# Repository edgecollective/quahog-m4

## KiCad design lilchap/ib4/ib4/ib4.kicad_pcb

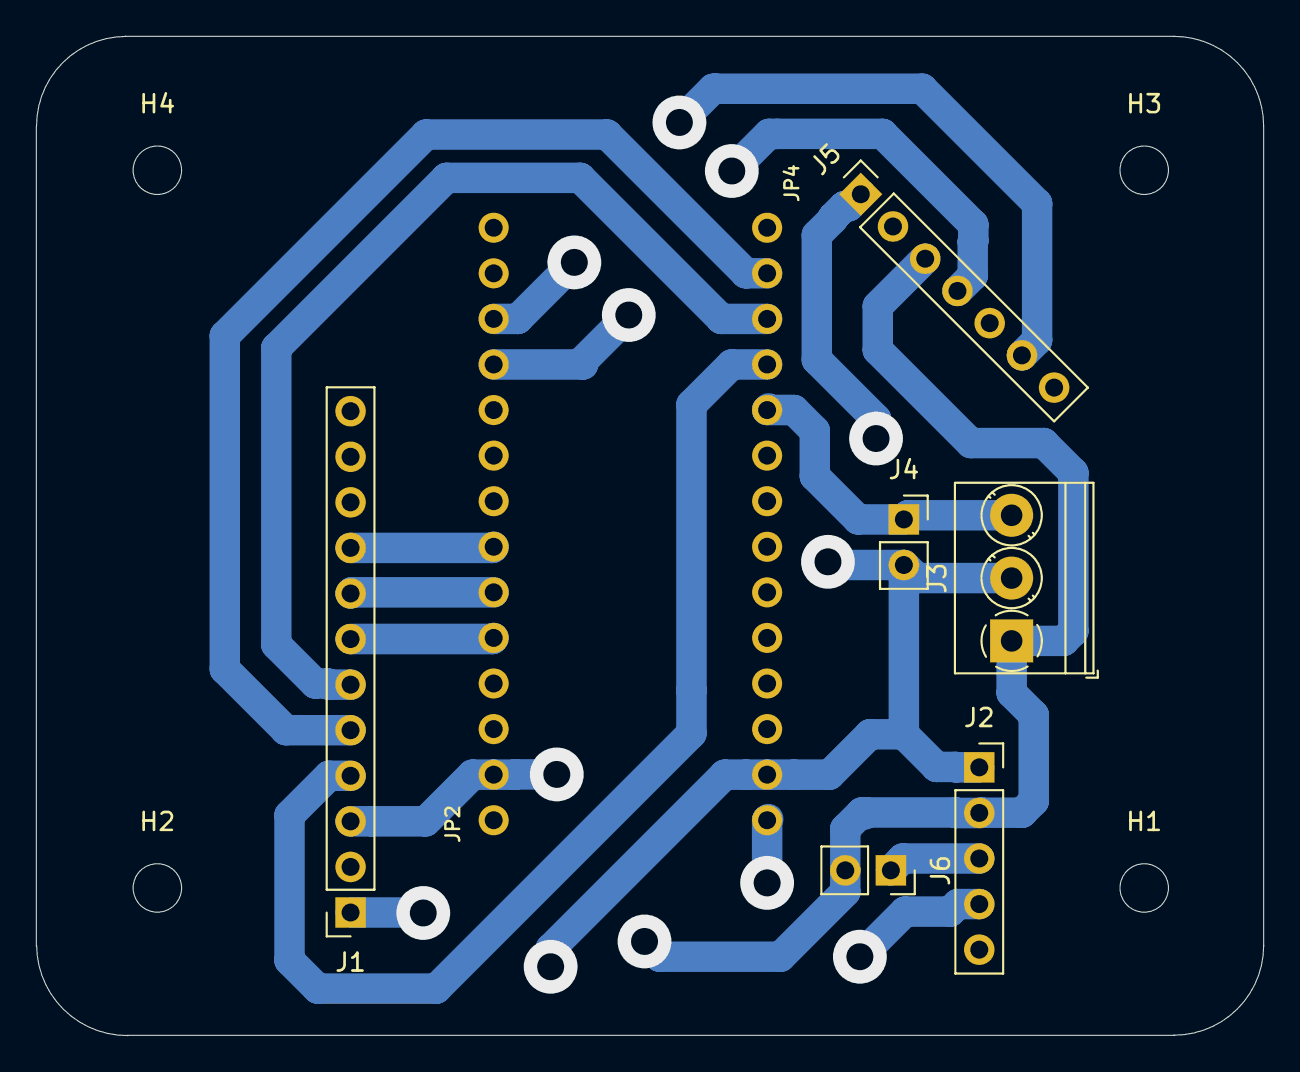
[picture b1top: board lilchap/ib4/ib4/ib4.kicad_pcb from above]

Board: 4 copper layers, 68.4 x 55.7 mm, 12 parts (0 on the bottom side), 13 nets.

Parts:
H1, H2, H3, H4: MountingHole; MountingHole_2.7mm_M2.5
J1: Conn_01x12_Female; PinSocket_1x12_P2.54mm_Vertical
J2: Conn_01x05_Female; PinSocket_1x05_P2.54mm_Vertical
J3: Conn_01x03_Female; TerminalBlock_Phoenix_PT-1,5-3-3.5-H_1x03_P3.50mm_Horizontal
J4, J6: Conn_01x02_Female; PinSocket_1x02_P2.54mm_Vertical
J5: Conn_01x07_Female; PinSocket_1x07_P2.54mm_Vertical
JP2, JP4: HEADER-1X14; 1X14_ROUND70

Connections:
+3V3: J1.1, J2.1, J3.2, J4.2, J5.1, JP4.13
A5: J3.3, J4.1, JP4.5
DELAY: J2.3, J6.1
DRV: J2.4, JP4.14
E_BUSY: J1.8, JP2.6
E_CS: J1.7, JP2.5
E_~RST: J1.9, JP2.7
GND: J1.3, J2.2, J3.1, J5.3, J6.2, JP2.2
MISO: J1.5, JP4.2
MOSI: J1.6, JP4.3
SCK: J1.4, JP4.4
SCL: J5.4, JP2.11
SDA: J5.6, JP2.12

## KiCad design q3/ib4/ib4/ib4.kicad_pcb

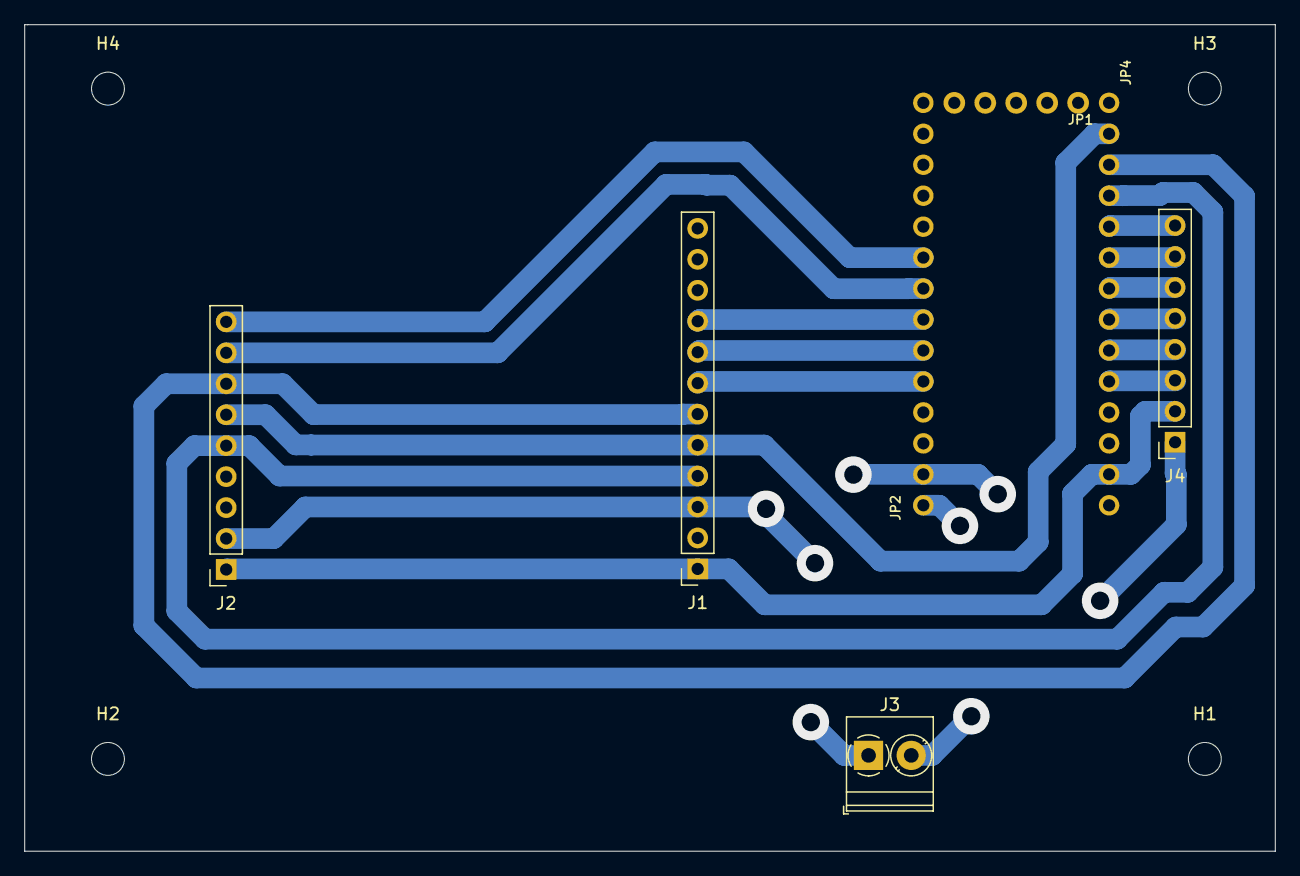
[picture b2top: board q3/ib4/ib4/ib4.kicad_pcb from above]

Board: 4 copper layers, 102.6 x 67.8 mm, 11 parts (0 on the bottom side), 17 nets.

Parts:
H1, H2, H3, H4: MountingHole; MountingHole_2.7mm_M2.5
J1: Conn_01x12_Female; PinSocket_1x12_P2.54mm_Vertical
J2: Conn_01x09_Female; PinSocket_1x09_P2.54mm_Vertical
J3: Screw_Terminal_01x02; TerminalBlock_Phoenix_PT-1,5-2-3.5-H_1x02_P3.50mm_Horizontal
J4: Conn_01x08_Female; PinSocket_1x08_P2.54mm_Vertical
JP1: HEADER-1X570MIL; 1X05_ROUND_70
JP2, JP4: HEADER-1X14; 1X14_ROUND70

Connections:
+3V3: J1.1, J2.1, J4.2, JP4.13
/A0: J4.3, JP4.10
/A1: J4.4, JP4.9
/A2: J4.5, JP4.8
/A3: J4.6, JP4.7
/A4: J4.7, JP4.6
/A5: J4.8, JP4.5
E_BUSY: J1.8, JP2.6
E_CS: J1.7, JP2.5
E_~RST: J1.9, JP2.7
GND: J1.3, J2.2, J3.1, J4.1, JP2.2
L_CS: J2.8, JP2.8
L_RST: J2.9, JP2.9
MISO: J1.5, J2.6, JP4.2
MOSI: J1.6, J2.7, JP4.3
SCK: J1.4, J2.5, JP4.4
VBAT: J3.2, JP2.1

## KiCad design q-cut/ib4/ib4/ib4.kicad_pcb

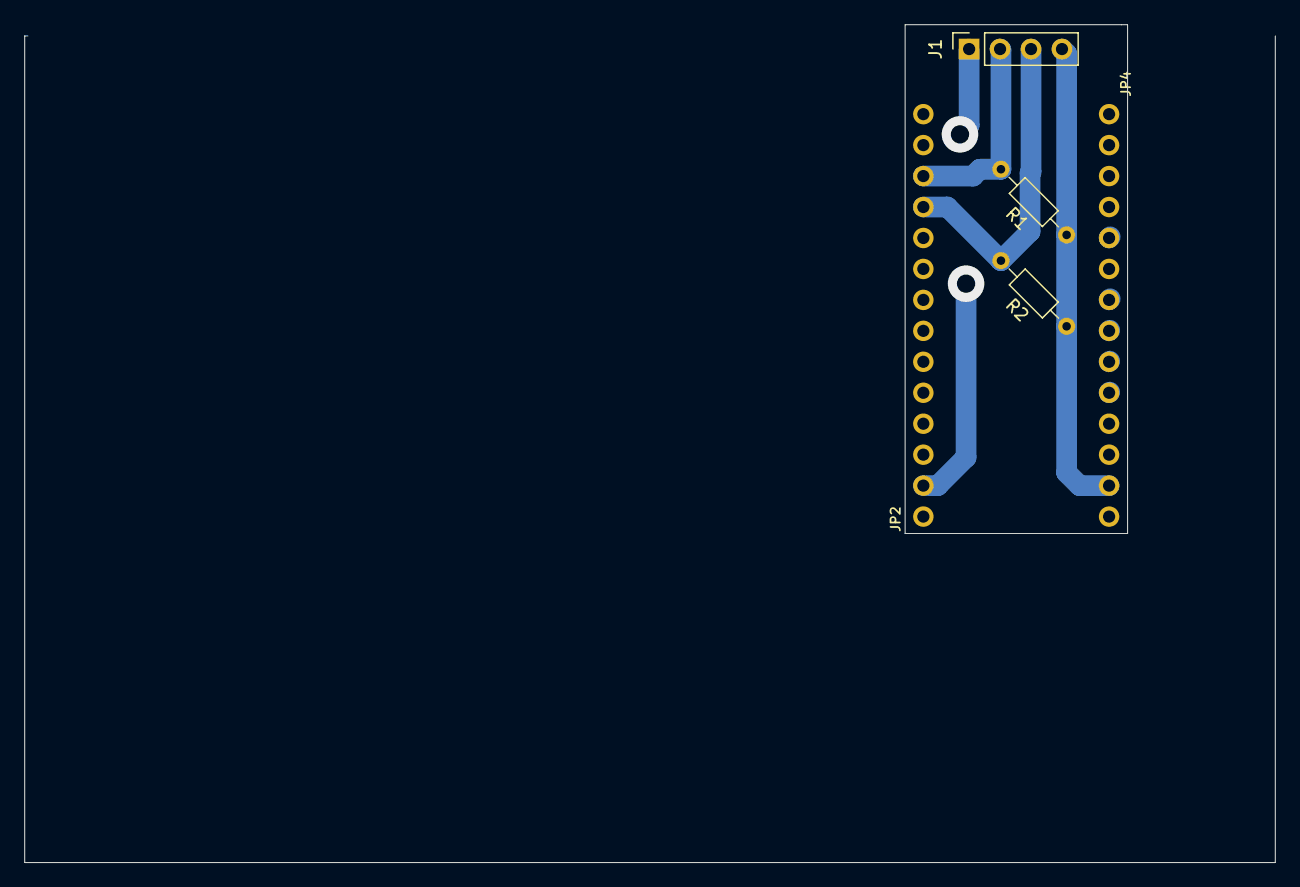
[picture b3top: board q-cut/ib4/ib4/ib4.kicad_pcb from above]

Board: 4 copper layers, 18.2 x 41.8 mm, 5 parts (0 on the bottom side), 4 nets.

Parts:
J1: Conn_01x04_Female; PinSocket_1x04_P2.54mm_Vertical
JP2, JP4: HEADER-1X14; 1X14_ROUND70
R1, R2: R; R_Axial_DIN0204_L3.6mm_D1.6mm_P7.62mm_Horizontal

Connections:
+3V3: J1.4, JP4.13, R1.1, R2.1
GND: J1.1, JP2.2
SCL: J1.3, JP2.11, R2.2
SDA: J1.2, JP2.12, R1.2

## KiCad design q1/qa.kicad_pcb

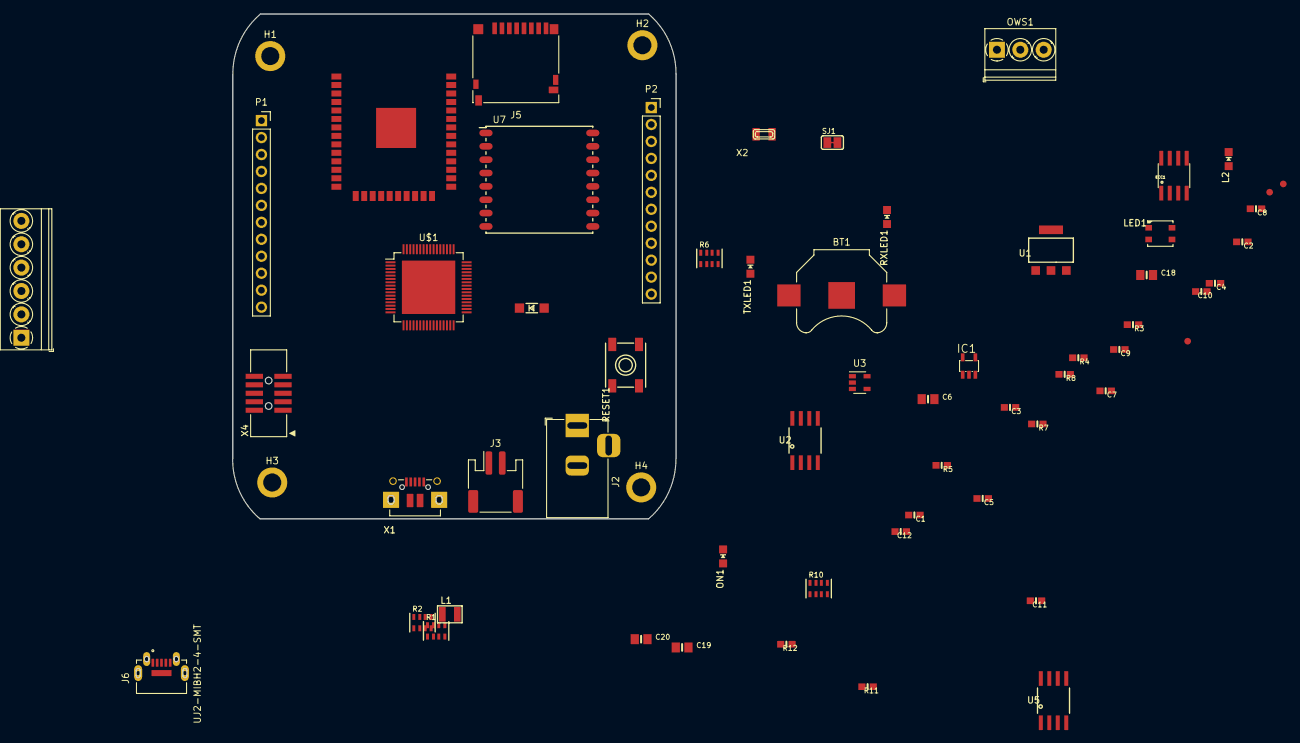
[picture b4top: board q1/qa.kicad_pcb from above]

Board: 2 copper layers, 63 parts (0 on the bottom side), 59 nets, no tracks yet.

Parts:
BT1: Battery_Cell; BatteryHolder_Keystone_3000_1x12mm
C1, C4: 22pF; 0603-NO
C2: 0.1uF; 0603-NO
C3, C7, C8, C9, C10, C11, C12: .1u; 0603-NO
C5: 1uF; 0603-NO
C6, C18, C19, C20: 10uF; 0805-NO
D1: D; SOD-123
ECC1: ATECC108; SOIC8
FD1, FD2, FD3: FIDUCIAL_1MM
H1, H2, H3, H4: MountingHole; MountingHole_2.7mm_M2.5_ISO14580_Pad
IC1: 74AHC1G125; SOT23-5L
J2: Barrel_Jack; BarrelJack_Horizontal
J3: Conn_01x02_Female; JST_PH_S2B-PH-SM4-TB_1x02-1MP_P2.00mm_Horizontal
J5: Connector_Micro_SD_Card; microSD_HC_Hirose_DM3D-SF
J6: UJ2-MIBH2-4-SMT; CUI_UJ2-MIBH2-4-SMT
J8: Screw_Terminal_01x06; TerminalBlock_Phoenix_PT-1,5-6-3.5-H_1x06_P3.50mm_Horizontal
L1: 10uH; INDUCTOR_1007
L2: RED; CHIPLED_0805_NOOUTLINE
LED1: WS2812B3535; LED3535
ON1: GREEN; CHIPLED_0805_NOOUTLINE
OWS1: Screw_Terminal_01x03; TerminalBlock_Phoenix_PT-1,5-3-3.5-H_1x03_P3.50mm_Horizontal
P1, P2: Conn_01x12_Female; PinSocket_1x12_P2.54mm_Vertical
R1: 10K; RESPACK_4X0603
R2, R6: R; RESPACK_4X0603
R3, R4, R5, R7: R; 0603-NO
R8, R12: 10K; 0603-NO
R10: 1K; RESPACK_4X0603
R11: 1K; 0603-NO
RESET1: EVQQ 6mm; EVQ-Q2_SMALLER
RXLED1: YELLOW; CHIPLED_0805_NOOUTLINE
SJ1: AREF_3V; SOLDERJUMPER_CLOSEDWIRE
TXLED1: YELLOW; CHIPLED_0805_NOOUTLINE
U1: tpl5110; SOT223-R
U2: CUI VX7805; SOIC8_208MIL
U3: AP2112K-3.3; SOT-23-5
U5: GD25Q16; SOIC8_208MIL
U7: RFM95HW; RFM95
U$1: ATSAMD51J19; TQFP-64-1EP_10x10mm_P0.5mm_EP8x8mm
X1: 20329; 4UCONN_20329_V2
X2: 32.768; XTAL3215
X4: 2x5 0.05" SWD; 2X05_1.27MM_BOX_POSTS
X5: ESP32_WROOM32; WROOM32

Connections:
3.3V: C7.2, C8.2, C9.2, C10.2, C11.2, C18.1, C19.1, C20.1, ECC1.8, IC1.5, J5.4, LED1.2, ON1.A, R1.1, R1.3, R1.4, R1.7, R8.2, R11.2, RXLED1.A, SJ1.1, TXLED1.A, U5.8, U7.13, U$1.8, U$1.21, U$1.34, U$1.48, U$1.56, X4.1, X5.2
/A0: P1.1, U$1.3
/A1: P1.2, U$1.14
/A2: P1.3, U$1.15
/A3: P1.4, U$1.61
/A4: P1.5, U$1.11
/A5: P1.6, U$1.12
/AREF: C12.1, SJ1.2, U$1.4
/D0: P1.7, U$1.44
/D2: P1.8, U$1.40
/D3: P1.9, U$1.39
/D4: P1.10, U$1.26
/D6: P1.11, U$1.28
/D13: P1.12, R10.8, U$1.35
/D+: J6.2, U$1.46, X1.D+
/D-: J6.3, U$1.45, X1.D-
/ESP_BUSY: U$1.5, X5.9
/ESP_CS: IC1.1, R1.2, U$1.32, X5.29
/ESP_GPIO0: U$1.62, X5.25
/ESP_MISO: IC1.2, X5.37
/ESP_RESET: R12.1, U$1.6, X5.3
/ESP_RTS: U$1.50, X5.31
/ESP_RXD: U$1.16, X5.35
/ESP_TXD: U$1.13, X5.34
/FLASH_CS: R8.1, U5.1, U$1.24
/FLASH_IO0: U5.5, U$1.17
/FLASH_IO1: U5.2, U$1.18
/FLASH_IO2: U5.3, U$1.19
/FLASH_IO3: U5.7, U$1.20
/FLASH_SCK: U5.6, U$1.23
/MISO: IC1.4, J5.7, U7.2, U$1.31
/MOSI: J5.3, U7.3, U$1.29, X5.13
/NEOPIX: LED1.1, U$1.49
/RXLED: R10.7, U$1.9
/SCK: J5.5, U7.4, U$1.30, X5.30
/SCL: ECC1.6, R1.5, U$1.64
/SDA: ECC1.5, R1.6, U$1.63
/SWCLK: R11.1, U$1.57, X4.4
/SWDIO: U$1.58, X4.2
/SWO: U$1.59, X4.6
/TXLED: R10.6, U$1.10
/~RESET: C2.2, R1.8, RESET1.B, RESET1.B', U$1.52, X4.10
GND: BT1.2, C1.2, C2.1, C3.1, C4.2, C5.2, C6.2, C7.1, C8.1, C9.1, C10.1, C11.1, C12.2, C18.2, C19.2, C20.2, ECC1.4, IC1.3, J2.2, J3.1, J5.6, J6.5, L2.C, LED1.4, R10.5, R12.2, RESET1.A, RESET1.A', U2.2, U3.2, U5.4, U7.1, U7.8, U7.10, U$1.7, U$1.22, U$1.33, U$1.47, U$1.54, X1.GND, X4.3, X4.5, X5.1, X5.15, X5.38, X5.P$1
unnamed: BT1.1, U1.1
unnamed: C1.1, U$1.2, X2.P$2
unnamed: C3.2, C5.1, C6.1, L1.P$1, U$1.53
unnamed: C4.1, U$1.1, X2.P$1
unnamed: R7.1, U3.1
unnamed: R2.2, U1.2
unnamed: R2.1, U1.3
unnamed: J6.SH1, J6.SH2, J6.SH3, J6.SH4, J6.SH5
unnamed: L1.P$2, U$1.55
unnamed: L2.A, R10.1
unnamed: ON1.C, R10.4
unnamed: R3.2, R4.2, U1.4
unnamed: R7.2, U3.3
unnamed: R10.2, RXLED1.C
unnamed: R10.3, TXLED1.C
VBUS: J6.1, X1.VBUS

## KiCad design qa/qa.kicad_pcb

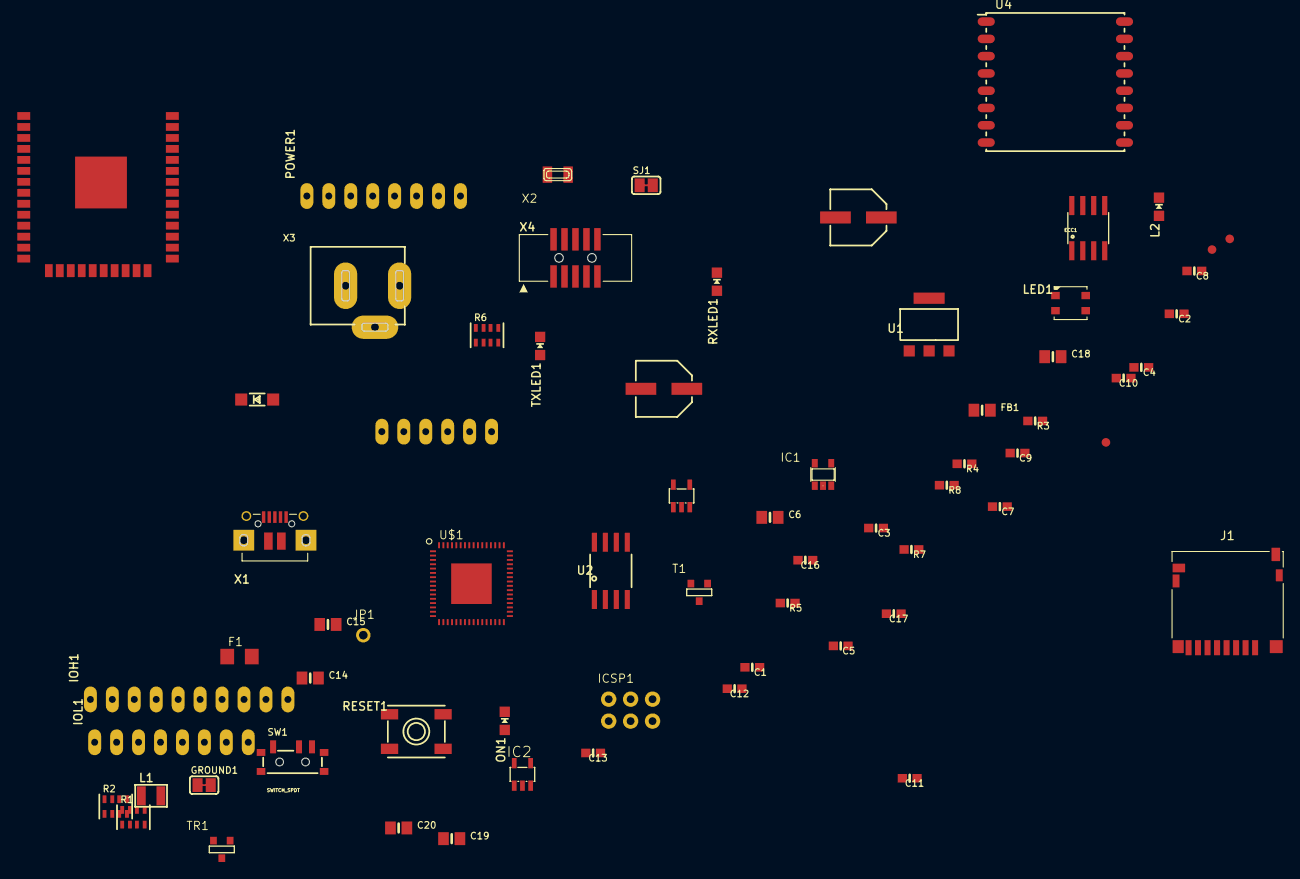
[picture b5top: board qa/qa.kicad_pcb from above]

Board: 2 copper layers, 68 parts (0 on the bottom side), 71 nets, no tracks yet.

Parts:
AD1: 20609; 1X06_OVALWAVE
C1, C4: 22pF; 0603-NO
C2, C13, C16: 0.1uF; 0603-NO
C3, C7, C8, C9, C10, C11, C12, C17: .1u; 0603-NO
C5: 1uF; 0603-NO
C6, C15, C18, C19, C20: 10uF; 0805-NO
C14: 0.1uF; 0805-NO
D1: MBR120; SOD-123
ECC1: ATECC108; SOIC8
F1: FUSE; R1206
FB1: FERRITE; 0805-NO
FD1, FD2, FD3: FIDUCIAL_1MM
GROUND1: SOLDERJUMPERCLOSED; SOLDERJUMPER_CLOSEDWIRE
IC1: 74LVC1G125D; SOT23-5
IC2: 74AHC1G125; SOT23-5L
ICSP1: 3x2 M; 2X03_ROUND_70MIL
IOH1: 20611; 1X10_OVALWAVE
IOL1: 20610; 1X08_OVALWAVE
J1: Connector_Micro_SD_Card; microSD_HC_Hirose_DM3D-SF
JP1: HEADER-1X1ROUND; 1X01_ROUND
L1: 10uH; INDUCTOR_1007
L2: RED; CHIPLED_0805_NOOUTLINE
LED1: WS2812B3535; LED3535
ON1: GREEN; CHIPLED_0805_NOOUTLINE
PC1: 47uF/25V; PANASONIC_D
PC2: 47uF+/6.3V+; PANASONIC_D
POWER1: 20610; 1X08_OVALWAVE
R1: 10K; RESPACK_4X0603
R2: 100K; RESPACK_4X0603
R3: 330R; 0603-NO
R4, R5, R8: 10K; 0603-NO
R6: 1K; RESPACK_4X0603
R7: 1K; 0603-NO
RESET1: EVQQ 6mm; EVQ-Q2_SMALLER
RXLED1: YELLOW; CHIPLED_0805_NOOUTLINE
SJ1: AREF_3V; SOLDERJUMPER_CLOSEDWIRE
SW1: SWITCH_SPDT; SPDT_SMT_SSSS811101
T1: DMP3098L-7; SOT-23
TR1: DMP3098L-7; SOT-23
TXLED1: YELLOW; CHIPLED_0805_NOOUTLINE
U1: NCP1117ST50T3G; SOT223-R
U2: GD25Q16; SOIC8_208MIL
U3: AP2112K-3.3; SOT23-DBV
U4: RFM95HW; RFM95
U$1: ATSAMD51J19; PQFN64-1
X1: 20329; 4UCONN_20329_V2
X2: 32.768; XTAL3215
X3: 2.1mm; DCJACK_2MM_PTH
X4: 2x5 0.05" SWD; 2X05_1.27MM_BOX_POSTS
X5: ESP32_WROOM32; WROOM32

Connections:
3.3V: C7.2, C8.2, C9.2, C10.2, C11.2, C15.2, C16.1, C17.2, C18.1, C19.1, C20.1, ECC1.8, IC1.5, IC2.5, LED1.2, ON1.A, POWER1.2, POWER1.4, R1.1, R1.3, R1.4, R1.7, R2.3, R4.2, R7.2, RXLED1.A, SJ1.1, TXLED1.A, U2.8, U3.5, U$1.8, U$1.21, U$1.34, U$1.48, U$1.56, X4.1, X5.2
+5V: C14.2, ICSP1.2, PC2.+, POWER1.5, TR1.2, U1.2, U1.4, U3.1, U3.3
/A0: AD1.1, U$1.3
/A1: AD1.2, U$1.14
/A2: AD1.3, U$1.15
/A3: AD1.4, U$1.61
/A4: AD1.5, U$1.11
/A5: AD1.6, U$1.12
/AREF: C12.1, IOH1.3, SJ1.2, U$1.4
/D0: IOL1.8, U$1.44
/D1: IOL1.7, U$1.43
/D2: IOL1.6, U$1.40
/D3: IOL1.5, U$1.39
/D4: IOL1.4, U$1.26
/D5: IOL1.3, U$1.27
/D6: IOL1.2, U$1.28
/D7: IOL1.1, U$1.25
/D8: IOH1.10, U$1.42
/D9: IOH1.9, U$1.41
/D10: IOH1.8, U$1.37
/D11: IOH1.7, U$1.38
/D12: IOH1.6, U$1.36
/D13: IOH1.5, R6.8, U$1.35
/D+: U$1.46, X1.D+
/D-: U$1.45, X1.D-
/ESP_BUSY: U$1.5, X5.9
/ESP_CS: IC2.1, R1.2, U$1.32, X5.29
/ESP_GPIO0: U$1.62, X5.25
/ESP_MISO: IC2.2, X5.37
/ESP_RESET: R8.1, U$1.6, X5.3
/ESP_RTS: U$1.50, X5.31
/ESP_RXD: U$1.16, X5.35
/ESP_TXD: U$1.13, X5.34
/FLASH_CS: R4.1, U2.1, U$1.24
/FLASH_IO0: U2.5, U$1.17
/FLASH_IO1: U2.2, U$1.18
/FLASH_IO2: U2.3, U$1.19
/FLASH_IO3: U2.7, U$1.20
/FLASH_SCK: U2.6, U$1.23
/MISO: IC2.4, ICSP1.1, U$1.31
/MOSI: ICSP1.4, U$1.29, X5.13
/NEOPIX: LED1.1, U$1.49
/RXLED: R6.7, U$1.9
/SCK: ICSP1.3, U$1.30, X5.30
/SCL: ECC1.6, IOH1.1, R1.5, U$1.64
/SDA: ECC1.5, IOH1.2, R1.6, U$1.63
/SWCLK: R7.1, U$1.57, X4.4
/SWDIO: U$1.58, X4.2
/SWO: U$1.59, X4.6
/TXLED: R6.6, U$1.10
/USBVCC: F1.2, TR1.1
/USB_HOSTEN: R3.2, U$1.51
/USHIELD: FB1.2, X1.BASE@1, X1.BASE@2, X1.SPRT@1, X1.SPRT@2, X1.SPRT@3, X1.SPRT@4
/VIN: C13.1, PC1.+, POWER1.8, R2.1, T1.1, U1.3
/~RESET: C2.2, ICSP1.5, POWER1.3, R1.8, RESET1.B, RESET1.B', U$1.52, X4.10
GND: C1.2, C2.1, C3.1, C4.2, C5.2, C6.2, C7.1, C8.1, C9.1, C10.1, C11.1, C12.2, C13.2, C14.1, C15.1, C16.2, C17.1, C18.2, C19.2, C20.2, ECC1.4, GROUND1.2, IC1.3, IC2.3, ICSP1.6, IOH1.4, L2.C, LED1.4, PC1.-, PC2.-, POWER1.6, POWER1.7, R2.2, R6.5, R8.2, RESET1.A, RESET1.A', SW1.A, U1.1, U2.4, U3.2, U$1.7, U$1.22, U$1.33, U$1.47, U$1.54, U$1.EXP, X1.GND, X3.GND, X3.GNDBREAK, X4.3, X4.5, X5.1, X5.15, X5.38, X5.P$1
unnamed: C1.1, U$1.2, X2.P$2
unnamed: C3.2, C5.1, C6.1, L1.P$1, U$1.53
unnamed: C4.1, U$1.1, X2.P$1
unnamed: D1.A, X3.PWR
unnamed: D1.C, R5.2, T1.2
unnamed: F1.1, X1.VBUS
unnamed: FB1.1, GROUND1.1
unnamed: IC1.1, IC1.2, R2.6, R3.1, X1.ID
unnamed: IC1.4, R2.7, R2.8, TR1.3
unnamed: JP1.1, R5.1, SW1.B, T1.3
unnamed: L1.P$2, U$1.55
unnamed: L2.A, R6.1
unnamed: ON1.C, R6.4
unnamed: R6.2, RXLED1.C
unnamed: R6.3, TXLED1.C
